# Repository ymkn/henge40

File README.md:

# Henge40

A compact 40% keyboard with 12-column row staggered layout in 12.75u width.

This keyboard was inspired by [Menhir](https://fruitykeeb.xyz/collections/menhir-collection/products/gb-menhir).

## Default Layout

You can also customize the layout using [Vial](https://get.vial.today/).

## Build Guide

See [Build Guide](doc/buildguide.md).

## License

This project is licensed under the MIT License, see the [LICENSE file](LICENSE) for details.

However, this does not apply to logo data (image files, KiCAD footprints, etc.) included in the resources of this project. Please contact us for secondary use.

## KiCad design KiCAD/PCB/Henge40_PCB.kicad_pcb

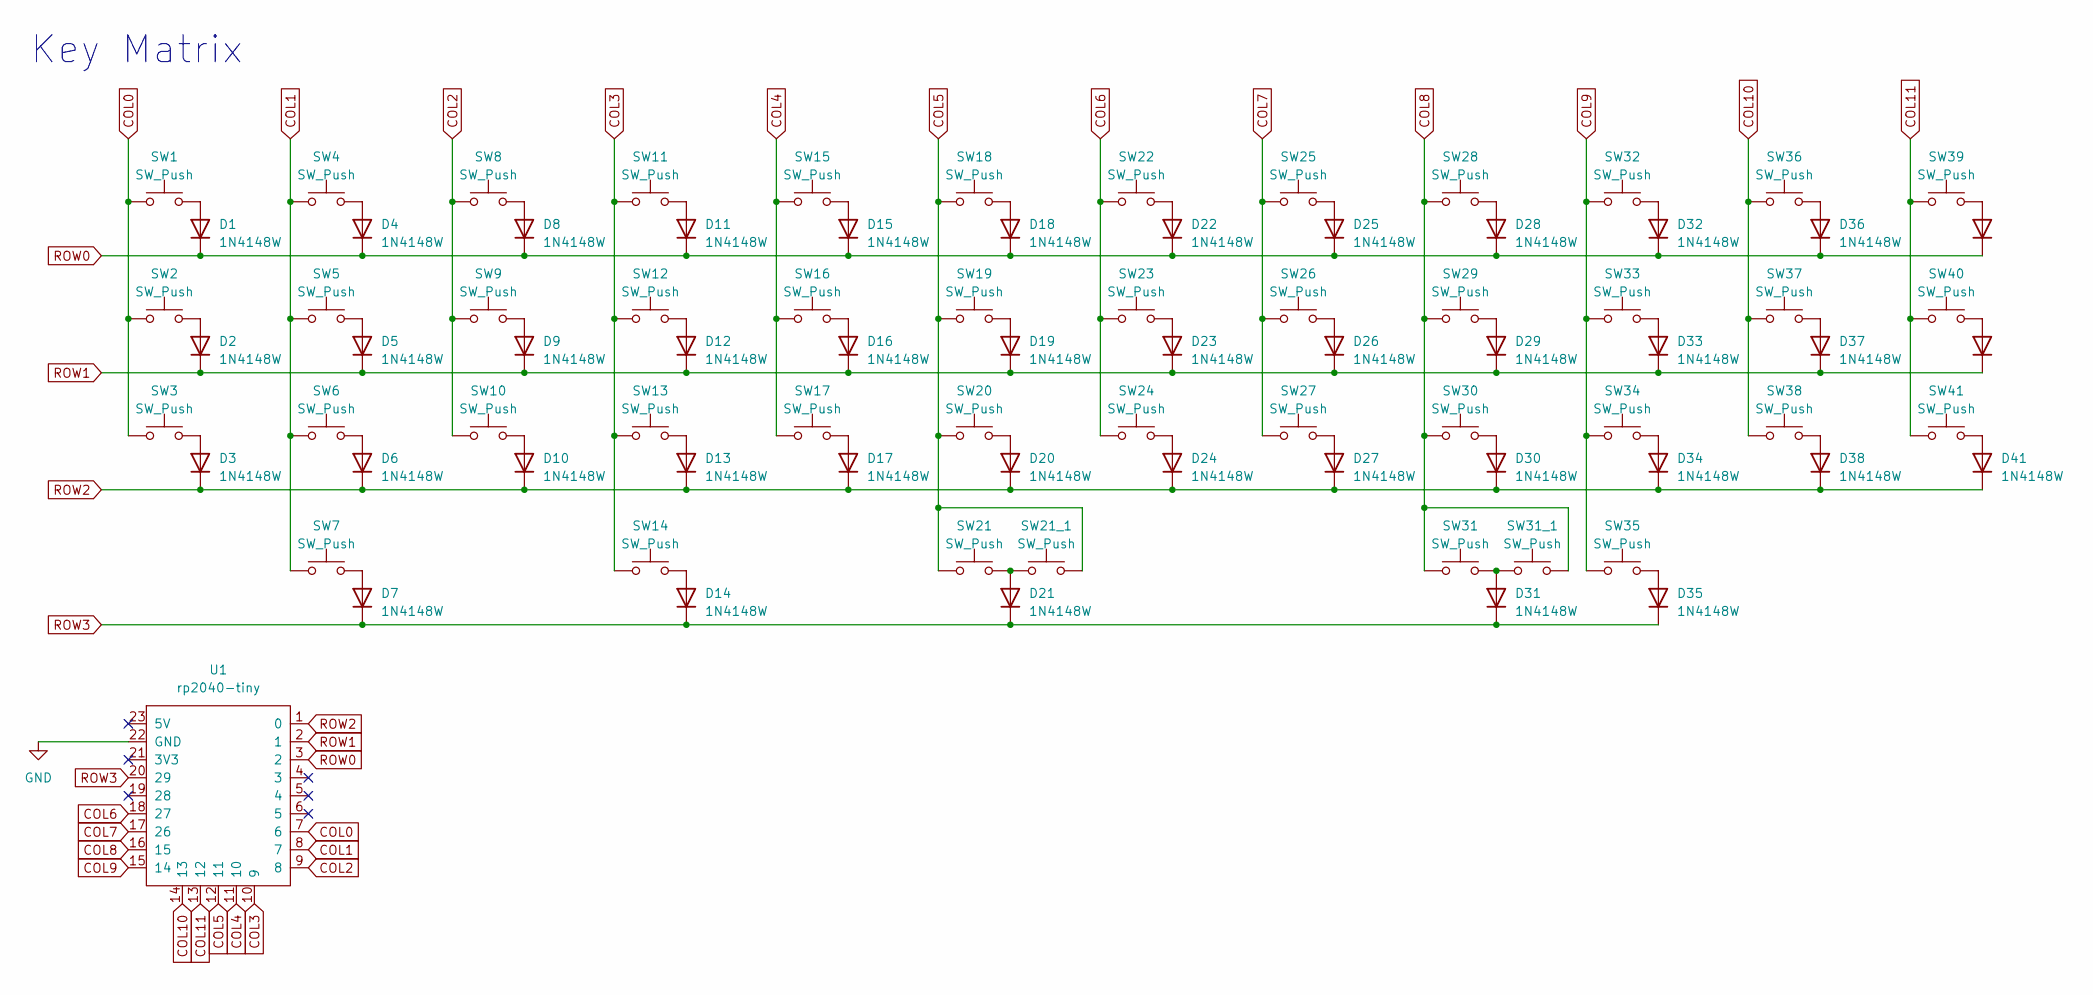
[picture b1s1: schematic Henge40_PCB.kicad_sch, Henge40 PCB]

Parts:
D1, D2, D3, D4, D5, D6, D7, D8, D9, D10, D11, D12, D13, D14, D15, D16, D17, D18, D19, D20, D21, D22, D23, D24, D25, D26, D27, D28, D29, D30, D31, D32, D33, D34, D35, D36, D37, D38, D39, D40, D41: 1N4148W; D_SOD-123; LCSC Parts # C81598
SW1, SW4, SW5, SW6, SW8, SW9, SW10, SW11, SW12, SW13, SW14, SW15, SW16, SW17, SW18, SW19, SW20, SW21, SW21_1, SW22, SW23, SW24, SW25, SW26, SW27, SW28, SW29, SW30, SW31, SW31_1, SW32, SW33, SW34, SW36, SW37, SW38, SW41: SW_Push; SW_MX_HS_CPG151101S11_1u; LCSC Parts # C18212911
SW2: SW_Push; SW_MX_HS_CPG151101S11_1.25u; LCSC Parts # C18212911
SW3, SW39: SW_Push; SW_MX_HS_CPG151101S11_1.75u; LCSC Parts # C18212911
SW7, SW35, SW40: SW_Push; SW_MX_HS_CPG151101S11_1.5u; LCSC Parts # C18212911
U1: rp2040-tiny; Waveshare_RP2040-Zero_SMD

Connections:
COL0: SW1.1, SW2.1, SW3.1, U1.7 (6)
COL1: SW4.1, SW5.1, SW6.1, SW7.1, U1.8 (7)
COL2: SW8.1, SW9.1, SW10.1, U1.9 (8)
COL3: SW11.1, SW12.1, SW13.1, SW14.1, U1.10 (9)
COL4: SW15.1, SW16.1, SW17.1, U1.11 (10)
COL5: SW18.1, SW19.1, SW20.1, SW21.1, SW21_1.2, U1.12 (11)
COL6: SW22.1, SW23.1, SW24.1, U1.18 (27)
COL7: SW25.1, SW26.1, SW27.1, U1.17 (26)
COL8: SW28.1, SW29.1, SW30.1, SW31.1, SW31_1.2, U1.16 (15)
COL9: SW32.1, SW33.1, SW34.1, SW35.1, U1.15 (14)
COL10: SW36.1, SW37.1, SW38.1, U1.14 (13)
COL11: SW39.1, SW40.1, SW41.1, U1.13 (12)
GND: U1.22 (GND)
unnamed: D1.2 (A), SW1.2
unnamed: D2.2 (A), SW2.2
unnamed: D3.2 (A), SW3.2
unnamed: D4.2 (A), SW4.2
unnamed: D5.2 (A), SW5.2
unnamed: D6.2 (A), SW6.2
unnamed: D7.2 (A), SW7.2
unnamed: D8.2 (A), SW8.2
unnamed: D9.2 (A), SW9.2
unnamed: D10.2 (A), SW10.2
unnamed: D11.2 (A), SW11.2
unnamed: D12.2 (A), SW12.2
unnamed: D13.2 (A), SW13.2
unnamed: D14.2 (A), SW14.2
unnamed: D15.2 (A), SW15.2
unnamed: D16.2 (A), SW16.2
unnamed: D17.2 (A), SW17.2
unnamed: D18.2 (A), SW18.2
unnamed: D19.2 (A), SW19.2
unnamed: D20.2 (A), SW20.2
unnamed: D21.2 (A), SW21.2, SW21_1.1
unnamed: D22.2 (A), SW22.2
unnamed: D23.2 (A), SW23.2
unnamed: D24.2 (A), SW24.2
unnamed: D25.2 (A), SW25.2
unnamed: D26.2 (A), SW26.2
unnamed: D27.2 (A), SW27.2
unnamed: D28.2 (A), SW28.2
unnamed: D29.2 (A), SW29.2
unnamed: D30.2 (A), SW30.2
unnamed: D31.2 (A), SW31.2, SW31_1.1
unnamed: D32.2 (A), SW32.2
unnamed: D33.2 (A), SW33.2
unnamed: D34.2 (A), SW34.2
unnamed: D35.2 (A), SW35.2
unnamed: D36.2 (A), SW36.2
unnamed: D37.2 (A), SW37.2
unnamed: D38.2 (A), SW38.2
unnamed: D39.2 (A), SW39.2
unnamed: D40.2 (A), SW40.2
unnamed: D41.2 (A), SW41.2
ROW0: D1.1 (K), D4.1 (K), D8.1 (K), D11.1 (K), D15.1 (K), D18.1 (K), D22.1 (K), D25.1 (K), D28.1 (K), D32.1 (K), D36.1 (K), D39.1 (K), U1.3 (2)
ROW1: D2.1 (K), D5.1 (K), D9.1 (K), D12.1 (K), D16.1 (K), D19.1 (K), D23.1 (K), D26.1 (K), D29.1 (K), D33.1 (K), D37.1 (K), D40.1 (K), U1.2 (1)
ROW2: D3.1 (K), D6.1 (K), D10.1 (K), D13.1 (K), D17.1 (K), D20.1 (K), D24.1 (K), D27.1 (K), D30.1 (K), D34.1 (K), D38.1 (K), D41.1 (K), U1.1 (0)
ROW3: D7.1 (K), D14.1 (K), D21.1 (K), D31.1 (K), D35.1 (K), U1.20 (29)

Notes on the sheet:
Key Matrix

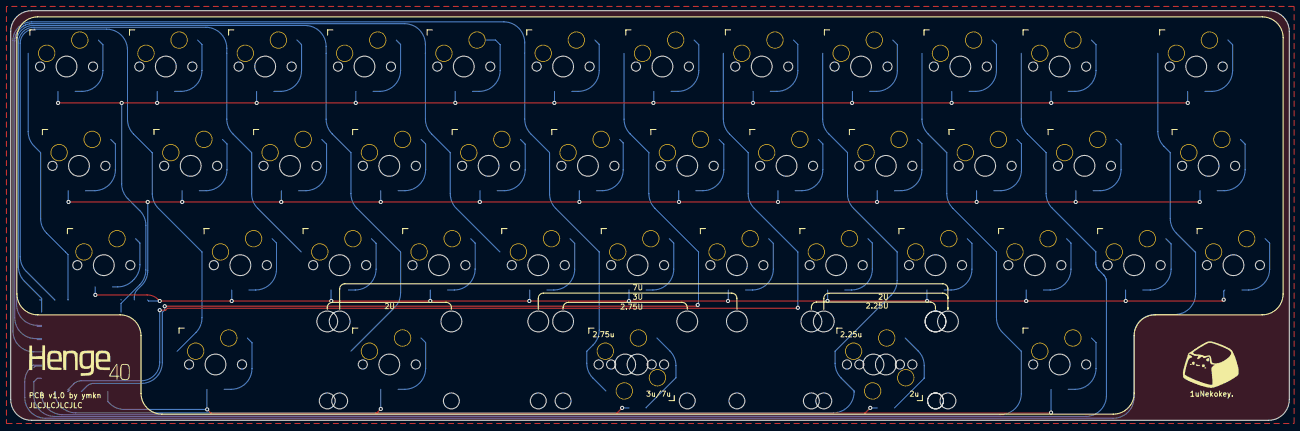
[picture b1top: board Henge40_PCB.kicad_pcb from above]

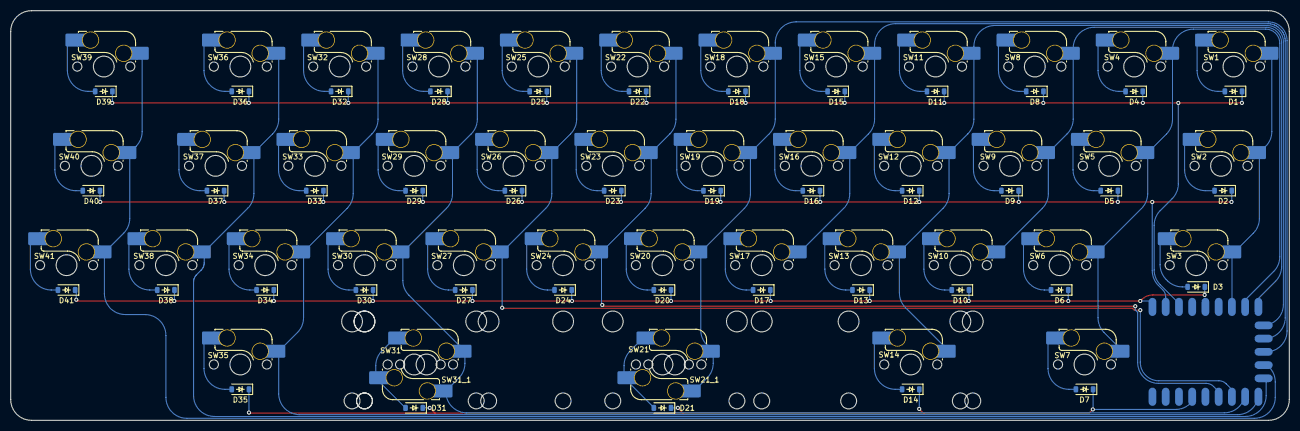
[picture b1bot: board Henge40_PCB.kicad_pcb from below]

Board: 2 copper layers, 245.3 x 78.6 mm, 85 parts (85 on the bottom side), 57 nets.

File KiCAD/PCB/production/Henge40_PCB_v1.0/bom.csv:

Designator,Footprint,Quantity,Value,LCSC Part #
"D1, D10, D11, D12, D13, D14, D15, D16, D17, D18, D19, D2, D20, D21, D22, D23, D24, D25, D26, D27, D28, D29, D3, D30, D31, D32, D33, D34, D35, D36, D37, D38, D39, D4, D40, D41, D5, D6, D7, D8, D9",D_SOD-123,41,1N4148W,
"SW1, SW10, SW11, SW12, SW13, SW14, SW15, SW16, SW17, SW18, SW19, SW20, SW21, SW21_1, SW22, SW23, SW24, SW25, SW26, SW27, SW28, SW29, SW30, SW31, SW31_1, SW32, SW33, SW34, SW36, SW37, SW38, SW4, SW41, SW5, SW6, SW8, SW9",SW_MX_HS_CPG151101S11_1u,37,SW_Push,
SW2,SW_MX_HS_CPG151101S11_1.25u,1,SW_Push,
"SW3, SW39",SW_MX_HS_CPG151101S11_1.75u,2,SW_Push,
"SW35, SW40, SW7",SW_MX_HS_CPG151101S11_1.5u,3,SW_Push,

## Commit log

2024-10-28 submoduleの追加
2024-10-28 v1.0製造断面
2024-10-28 ファームウェア
2024-10-28 v1.1ケース製造データ
2024-10-28 READMEの修正
2024-12-27 最新のymknlibsに切り替え
2024-12-27 1stロット量産断面
2024-12-27 READMEを整備
2024-12-27 ファームウェアのソースを追加
2024-12-27 移動元のファイルを削除
2024-12-27 Damping Ballのモデルを追加
2024-12-27 ファームウェアのソースのREADMEを追加
2024-12-27 READMEの画像が荒かったのを修正
2025-01-12 ビルドガイドの追加
2025-01-12 v1.0断面
2025-01-13 脱字とBOOTHリンク修正
2025-01-13 ケース呼称の変更
2025-02-24 ロット違いの写真追加、サポートポリシーのリンク追加
